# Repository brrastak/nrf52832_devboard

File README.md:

# nRF52832 development board

The project main intension is the first experiment in designing bluetooth hardware. Design is **not tested!**

The TI antenna SWRA117D is used (AN 043).

USB connector and voltage regulator circuitry are optional and only provide power.

## Known issues

It turns out that using P10 as an LED pin is not the best idea, as it is one of the NFC pins. To use it as a GPIO, you first need to disable the NFC pin protection. Using Rust and the nRF52832 PAC, this is done with the following code (the dedicated NVRAM register value should be set once and the new configuration is taken into account after MCU reset):

```rust
p.NVMC.config.write(|w| w.wen().wen());
p.UICR.nfcpins.write(|w| w.protect().disabled());
p.NVMC.config.reset();
```

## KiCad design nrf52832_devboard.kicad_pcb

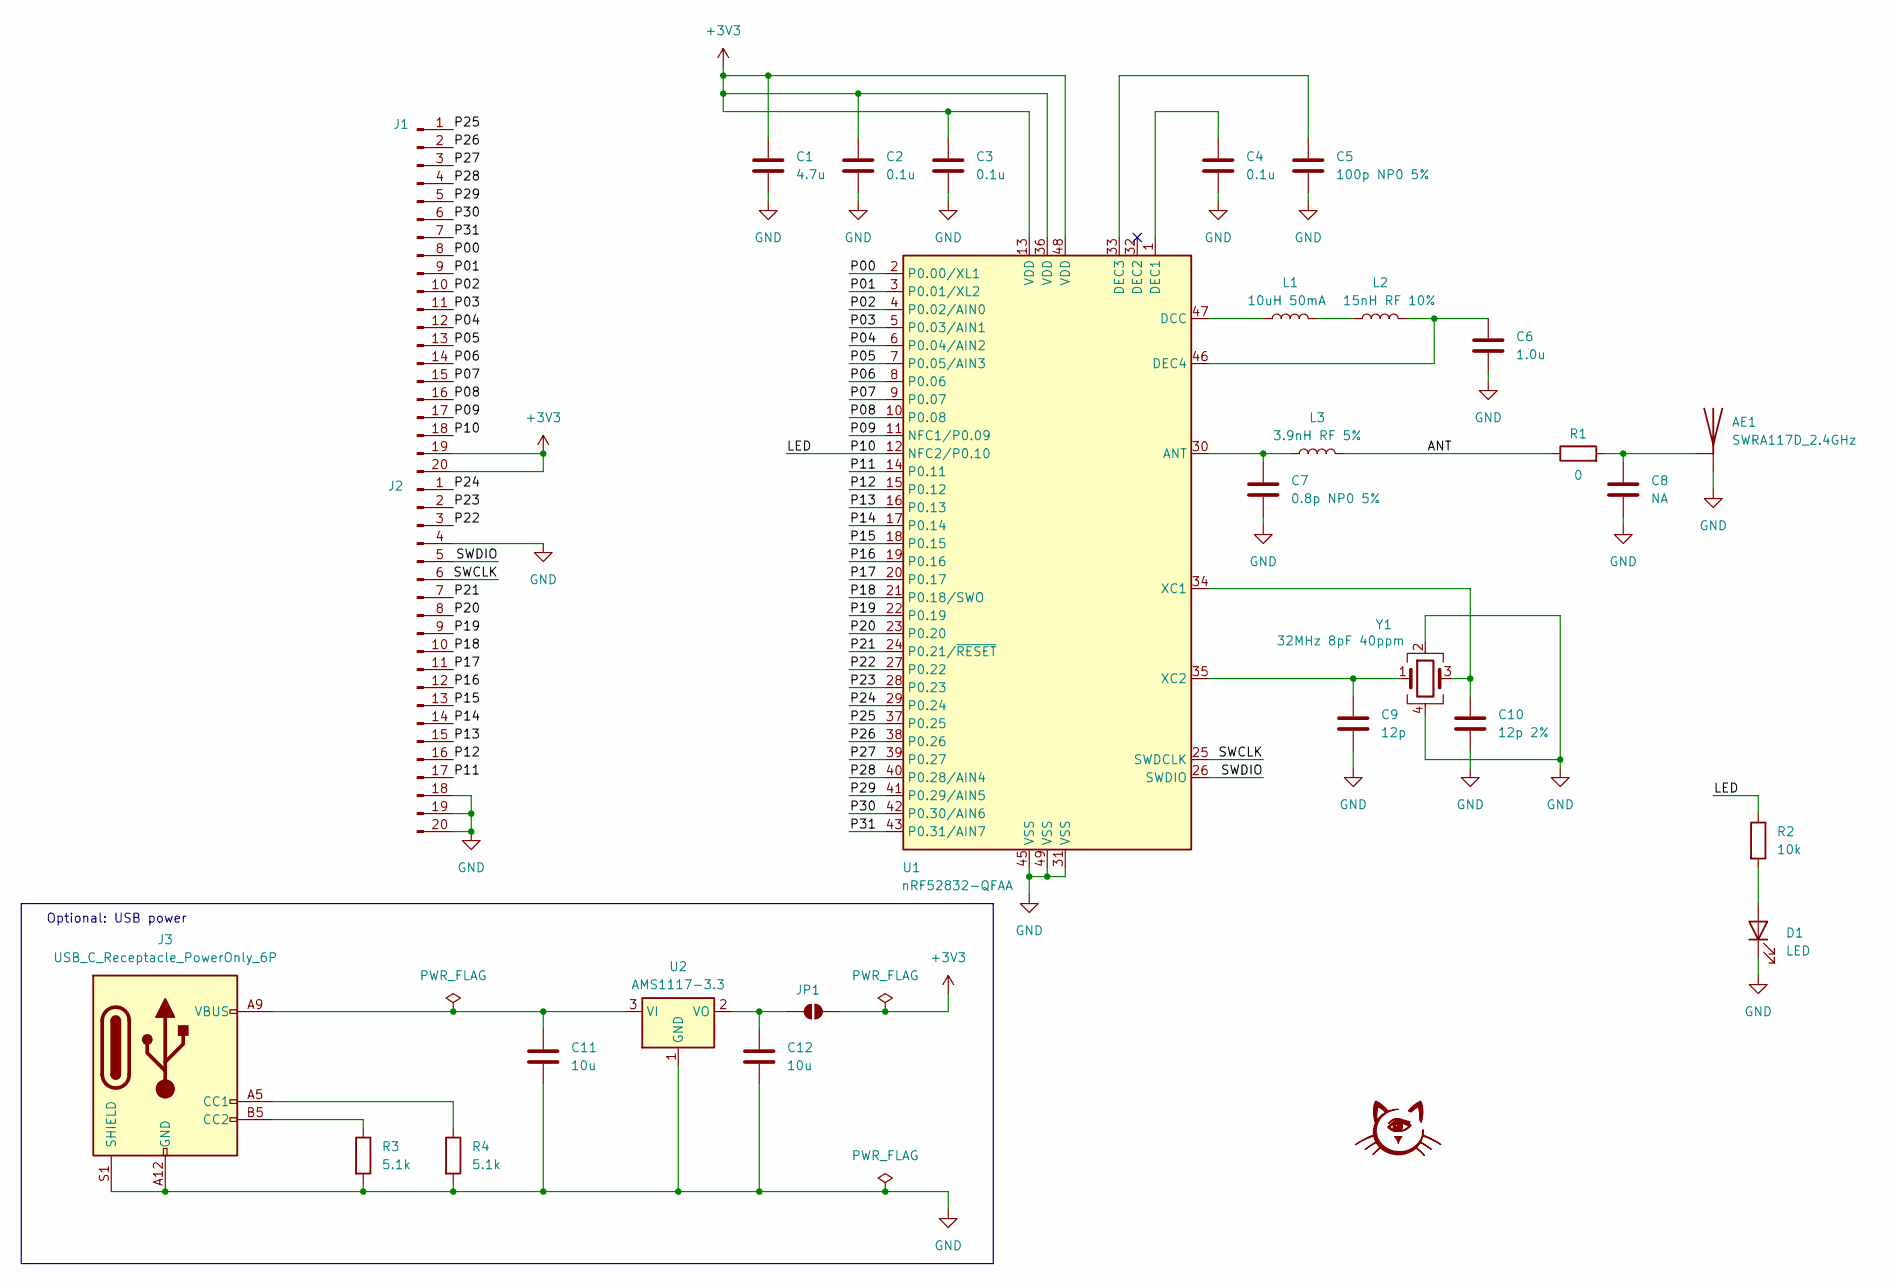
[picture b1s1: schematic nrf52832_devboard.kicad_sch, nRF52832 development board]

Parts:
AE1: SWRA117D_2.4GHz; Texas_SWRA117D_2.4GHz_Left
C1: 4.7u; C_0603_1608Metric_Pad1.08x0.95mm_HandSolder
C2, C3, C4: 0.1u; C_0402_1005Metric_Pad0.74x0.62mm_HandSolder
C5: 100p NP0 5%; C_0402_1005Metric_Pad0.74x0.62mm_HandSolder
C6: 1.0u; C_0603_1608Metric_Pad1.08x0.95mm_HandSolder
C7: 0.8p NP0 5%; C_0402_1005Metric
C8: NA; C_0402_1005Metric
C9: 12p; C_0402_1005Metric_Pad0.74x0.62mm_HandSolder
C10: 12p 2%; C_0402_1005Metric_Pad0.74x0.62mm_HandSolder
C11, C12: 10u; C_0603_1608Metric_Pad1.08x0.95mm_HandSolder
D1: LED; LED_0603_1608Metric_Pad1.05x0.95mm_HandSolder
G1: stamp
J1, J2: Conn_01x20_Pin; PinHeader_1x20_P2.54mm_Vertical
J3: USB_C_Receptacle_PowerOnly_6P; USB_C_Receptacle_GCT_USB4125-xx-x_6P_TopMnt_Horizontal
JP1: SolderJumper_2_Open; SolderJumper-2_P1.3mm_Open_RoundedPad1.0x1.5mm
L1: 10uH 50mA; L_0603_1608Metric_Pad1.05x0.95mm_HandSolder
L2: 15nH RF 10%; L_0402_1005Metric_Pad0.77x0.64mm_HandSolder
L3: 3.9nH RF 5%; L_0402_1005Metric
R1: 0; R_0402_1005Metric
R2: 10k; R_0603_1608Metric_Pad0.98x0.95mm_HandSolder
R3, R4: 5.1k; R_0603_1608Metric_Pad0.98x0.95mm_HandSolder
U1: nRF52832-QFAA; QFN-48-1EP_6x6mm_P0.4mm_EP4.6x4.6mm
U2: AMS1117-3.3; SOT-223-3_TabPin2
Y1: 32MHz 8pF 40ppm; Crystal_SMD_2016-4Pin_2.0x1.6mm

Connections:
+3V3: C1.1, C2.1, C3.1, J1.19, J1.20, JP1.2 (B), U1.13 (VDD), U1.36 (VDD), U1.48 (VDD)
/ANT: L3.2, R1.1
/LED: J1.18, R2.1, U1.12 (NFC2/P0.10)
/P00: J1.8, U1.2 (P0.00/XL1)
/P01: J1.9, U1.3 (P0.01/XL2)
/P02: J1.10, U1.4 (P0.02/AIN0)
/P03: J1.11, U1.5 (P0.03/AIN1)
/P04: J1.12, U1.6 (P0.04/AIN2)
/P05: J1.13, U1.7 (P0.05/AIN3)
/P06: J1.14, U1.8 (P0.06)
/P07: J1.15, U1.9 (P0.07)
/P08: J1.16, U1.10 (P0.08)
/P09: J1.17, U1.11 (NFC1/P0.09)
/P11: J2.17, U1.14 (P0.11)
/P12: J2.16, U1.15 (P0.12)
/P13: J2.15, U1.16 (P0.13)
/P14: J2.14, U1.17 (P0.14)
/P15: J2.13, U1.18 (P0.15)
/P16: J2.12, U1.19 (P0.16)
/P17: J2.11, U1.20 (P0.17)
/P18: J2.10, U1.21 (P0.18/SWO)
/P19: J2.9, U1.22 (P0.19)
/P20: J2.8, U1.23 (P0.20)
/P21: J2.7, U1.24 (P0.21/~RESET)
/P22: J2.3, U1.27 (P0.22)
/P23: J2.2, U1.28 (P0.23)
/P24: J2.1, U1.29 (P0.24)
/P25: J1.1, U1.37 (P0.25)
/P26: J1.2, U1.38 (P0.26)
/P27: J1.3, U1.39 (P0.27)
/P28: J1.4, U1.40 (P0.28/AIN4)
/P29: J1.5, U1.41 (P0.29/AIN5)
/P30: J1.6, U1.42 (P0.30/AIN6)
/P31: J1.7, U1.43 (P0.31/AIN7)
/SWCLK: J2.6, U1.25 (SWDCLK)
/SWDIO: J2.5, U1.26 (SWDIO)
GND: AE1.2 (A), C1.2, C2.2, C3.2, C4.2, C5.2, C6.2, C7.2, C8.2, C9.2, C10.2, C11.2, C12.2, D1.1 (K), J2.4, J2.18, J2.19, J2.20, J3.A12 (GND), J3.B12 (GND), J3.S1 (SHIELD), R3.2, R4.2, U1.31 (VSS), U1.45 (VSS), U1.49 (VSS), U2.1 (GND), Y1.2, Y1.4
unnamed: AE1.1 (A), C8.1, R1.2
unnamed: D1.2 (A), R2.2
unnamed: J3.A5 (CC1), R4.1
unnamed: J3.B5 (CC2), R3.1
unnamed: C12.1, JP1.1 (A), U2.2 (VO)
unnamed: L1.2, L2.1
unnamed: C7.1, L3.1, U1.30 (ANT)
unnamed: L1.1, U1.47 (DCC)
unnamed: C4.1, U1.1 (DEC1)
unnamed: C5.1, U1.33 (DEC3)
unnamed: C6.1, L2.2, U1.46 (DEC4)
unnamed: C10.1, U1.34 (XC1), Y1.3
unnamed: C9.1, U1.35 (XC2), Y1.1
unnamed: C11.1, J3.A9 (VBUS), J3.B9 (VBUS), U2.3 (VI)

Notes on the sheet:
Optional: USB power

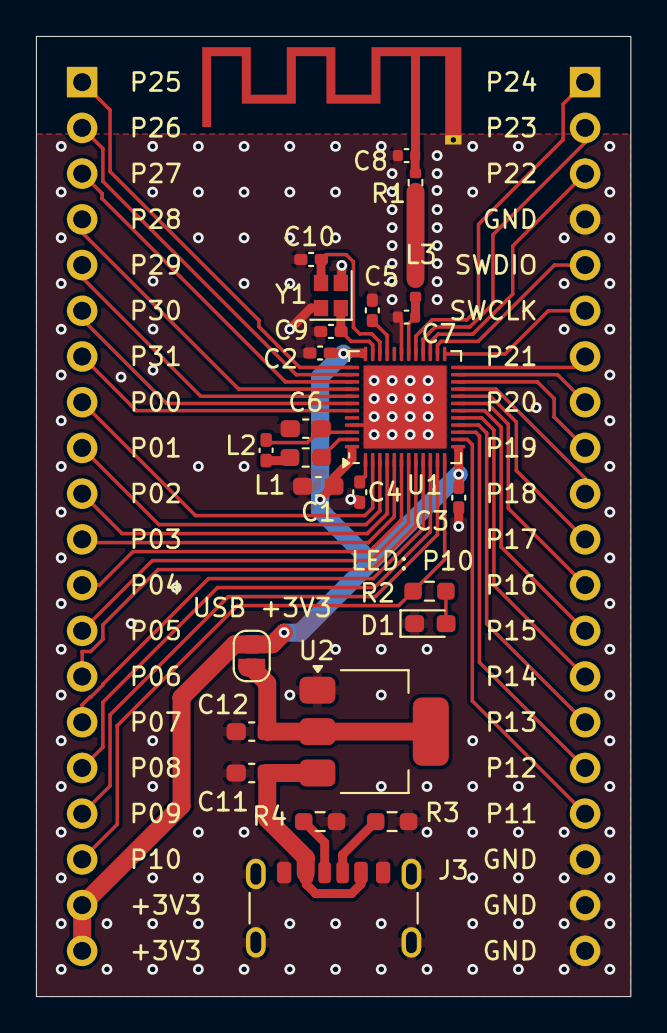
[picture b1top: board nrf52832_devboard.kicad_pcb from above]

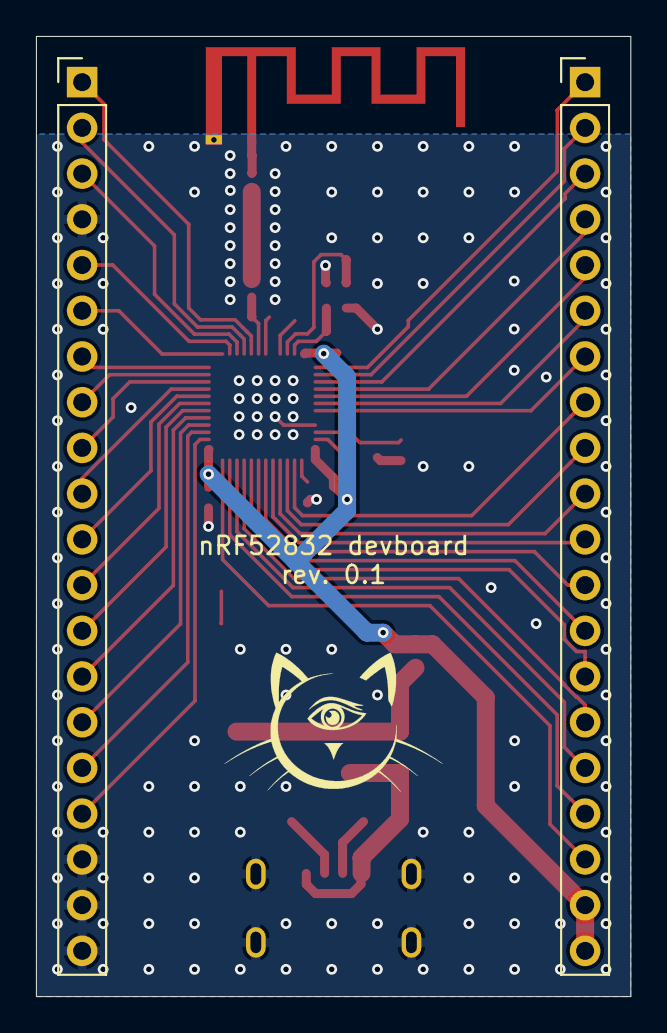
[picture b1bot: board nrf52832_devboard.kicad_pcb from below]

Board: 2 copper layers, 33.0 x 53.3 mm, 29 parts (3 on the bottom side), 51 nets.

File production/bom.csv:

"Id";"Designator";"Footprint";"Quantity";"Designation";"Supplier and ref";
1;"J3";"USB_C_Receptacle_GCT_USB4125-xx-x_6P_TopMnt_Horizontal";1;"USB_C_Receptacle_PowerOnly_6P";;;
2;"D1";"LED_0603_1608Metric_Pad1.05x0.95mm_HandSolder";1;"LED";;;
3;"R3,R4";"R_0603_1608Metric_Pad0.98x0.95mm_HandSolder";2;"5.1k";;;
4;"C7";"C_0402_1005Metric";1;"0.8p NP0 5%";;;
5;"Y1";"Crystal_SMD_2016-4Pin_2.0x1.6mm";1;"32MHz 8pF 40ppm";;;
6;"C1";"C_0603_1608Metric_Pad1.08x0.95mm_HandSolder";1;"4.7u";;;
7;"C6";"C_0603_1608Metric_Pad1.08x0.95mm_HandSolder";1;"1.0u";;;
8;"C5";"C_0402_1005Metric_Pad0.74x0.62mm_HandSolder";1;"100p NP0 5%";;;
9;"C4,C2,C3";"C_0402_1005Metric_Pad0.74x0.62mm_HandSolder";3;"0.1u";;;
10;"AE1";"Texas_SWRA117D_2.4GHz_Left";1;"SWRA117D_2.4GHz";;;
11;"L1";"L_0603_1608Metric_Pad1.05x0.95mm_HandSolder";1;"10uH 50mA";;;
12;"C8";"C_0402_1005Metric";1;"NA";;;
13;"R1";"R_0402_1005Metric";1;"0";;;
14;"U1";"QFN-48-1EP_6x6mm_P0.4mm_EP4.6x4.6mm";1;"nRF52832-QFAA";;;
15;"C11,C12";"C_0603_1608Metric_Pad1.08x0.95mm_HandSolder";2;"10u";;;
16;"L3";"L_0402_1005Metric";1;"3.9nH RF 5%";;;
17;"R2";"R_0603_1608Metric_Pad0.98x0.95mm_HandSolder";1;"10k";;;
18;"L2";"L_0402_1005Metric_Pad0.77x0.64mm_HandSolder";1;"15nH RF 10%";;;
19;"C9";"C_0402_1005Metric_Pad0.74x0.62mm_HandSolder";1;"12p";;;
20;"U2";"SOT-223-3_TabPin2";1;"AMS1117-3.3";;;
21;"C10";"C_0402_1005Metric_Pad0.74x0.62mm_HandSolder";1;"12p 2%";;;
22;"G1";"stamp";1;"stamp";;;
23;"J2,J1";"PinHeader_1x20_P2.54mm_Vertical";2;"Conn_01x20_Pin";;;

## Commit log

2024-10-04 Initial commit rev. 0.1
2024-10-04 Update BOM
